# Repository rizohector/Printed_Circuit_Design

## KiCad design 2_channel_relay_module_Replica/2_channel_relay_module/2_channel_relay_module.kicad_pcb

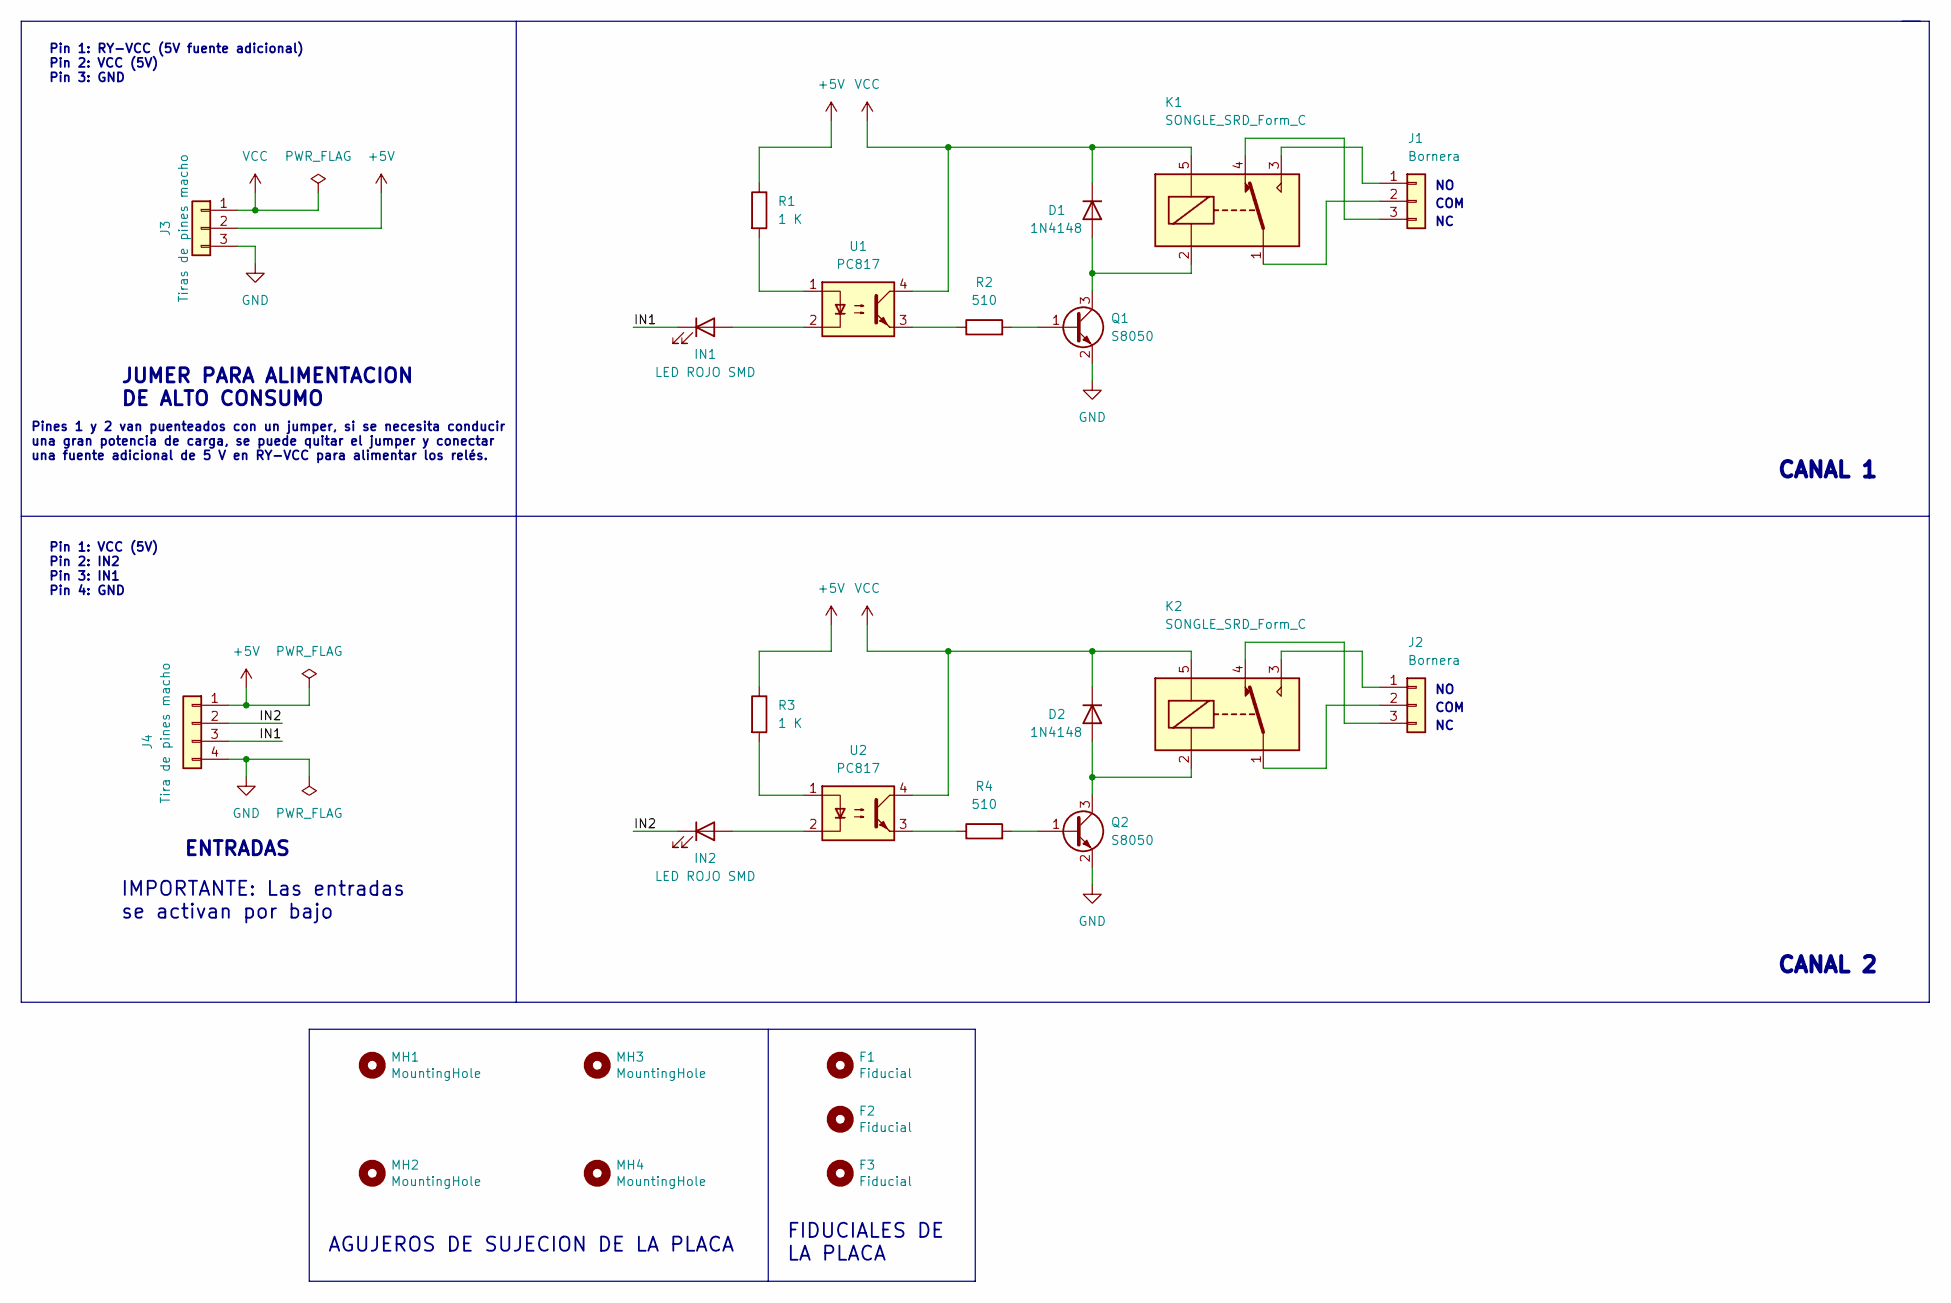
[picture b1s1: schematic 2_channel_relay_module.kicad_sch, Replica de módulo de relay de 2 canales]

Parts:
D1, D2: 1N4148; LED_1206_3216Metric
F1, F2, F3: Fiducial; Fiducial_0.5mm_Mask1.5mm
IN1, IN2: LED ROJO SMD; LED_1206_3216Metric
J1, J2: Bornera; TerminalBlock_bornier-3_P5.08mm
J3: Tiras de pines macho; PinHeader_1x03_P2.54mm_Vertical
J4: Tira de pines macho; PinHeader_1x04_P2.54mm_Vertical
K1, K2: SONGLE_SRD_Form_C; Relay_SPDT_SONGLE_SRD_Series_Form_C
MH1, MH2, MH3, MH4: MountingHole; MountingHole_3.2mm_M3_ISO14580
Q1, Q2: S8050; SOT-23
R1, R3: 1 K; R_1206_3216Metric
R2, R4: 510; R_1206_3216Metric
U1, U2: PC817; DIP-4_W7.62mm

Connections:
+5V: J3.2, J4.1, R1.1, R3.1
/IN1: IN1.1 (K), J4.3
/IN2: IN2.1 (K), J4.2
GND: J3.3, J4.4, Q1.2 (E), Q2.2 (E)
unnamed: D1.2 (A), K1.2, Q1.3 (C)
unnamed: D2.2 (A), K2.2, Q2.3 (C)
unnamed: IN1.2 (A), U1.2
unnamed: IN2.2 (A), U2.2
unnamed: J1.2, K1.1
unnamed: J2.2, K2.1
unnamed: J1.1, K1.3
unnamed: J1.3, K1.4
unnamed: J2.1, K2.3
unnamed: J2.3, K2.4
unnamed: Q1.1 (B), R2.2
unnamed: Q2.1 (B), R4.2
unnamed: R1.2, U1.1
unnamed: R2.1, U1.3
unnamed: R3.2, U2.1
unnamed: R4.1, U2.3
VCC: D1.1 (K), D2.1 (K), J3.1, K1.5, K2.5, U1.4, U2.4

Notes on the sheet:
CANAL 1
COM
Pines 1 y 2 van puenteados con un jumper, si se necesita conducir una gran potencia de carga, se puede quitar el jumper y conectar una fuente adicional de 5 V en RY-VCC para alimentar los relés.
JUMER PARA ALIMENTACION DE ALTO CONSUMO
ENTRADAS
FIDUCIALES DE LA PLACA
IMPORTANTE: Las entradas se activan por bajo
Pin 1: VCC (5V) Pin 2: IN2 Pin 3: IN1 Pin 4: GND
CANAL 2
AGUJEROS DE SUJECION DE LA PLACA
Pin 1: RY-VCC (5V fuente adicional) Pin 2: VCC (5V) Pin 3: GND

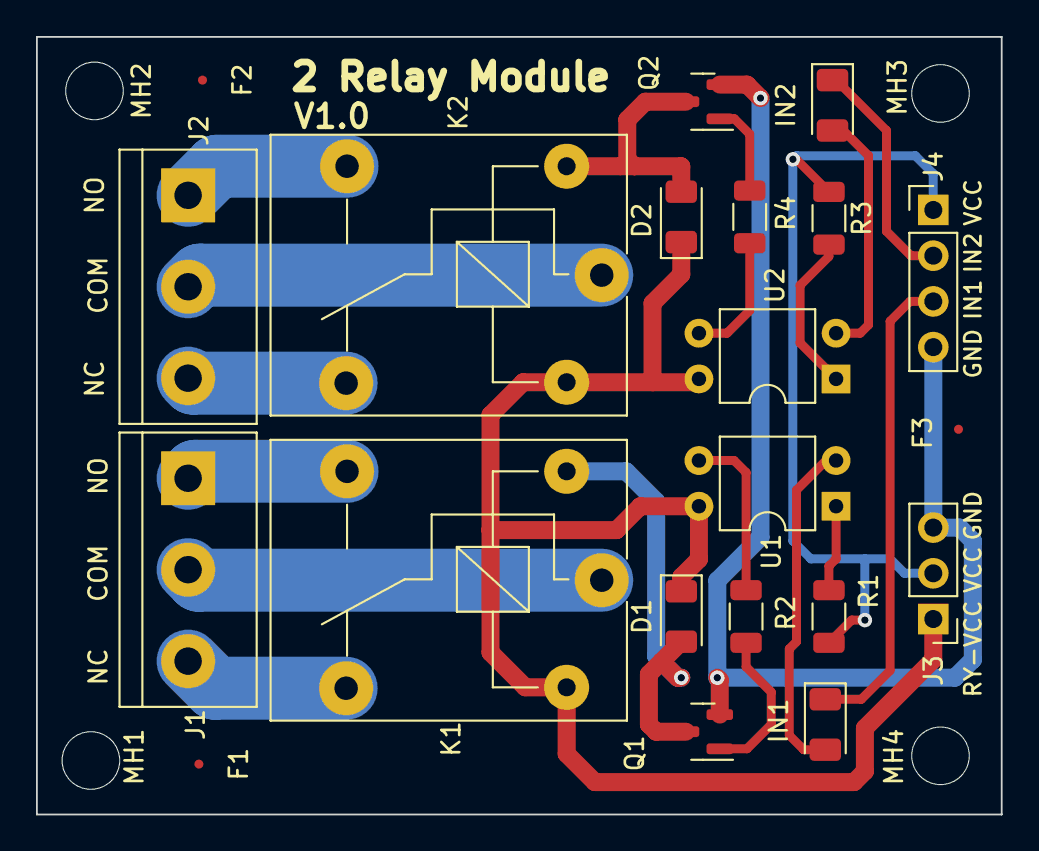
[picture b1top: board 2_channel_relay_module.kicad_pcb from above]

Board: 2 copper layers, 53.6 x 43.2 mm, 25 parts (0 on the bottom side), 21 nets.

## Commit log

2022-07-28 commit_01
2022-08-10 commit_02

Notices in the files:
2_channel_relay_module_Replica/2_channel_relay_module/2_channel_relay_module.kicad_sch:
Licencia: CERN OHL V1.0
